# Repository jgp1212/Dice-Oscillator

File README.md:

# Dice-Oscillator
A simple pcb design for a 40106 square wave oscillator drone.

NOTE: This Readme is still a work in progress

Control 6 oscillators using 6 potentiometers. 

Additional pins have been exposed to allow for potential vactrol implementations, or maybe you have a potentiometer that doesnt fit the footprint. 
Use cables to solder to these points.

Can be powered by 5-12V, using 5V will output roughly ~4Vpp, while 12V will output a 10Vpp.
Power supply must be center positive, I have blown up several CD40106BE by accident by using center negative by accident.

BOM:
-  1 x CD40106BE IC
  - 

-  1 x 2.1mm Power jack OR 1 x 16 pin eurorackstyle header. USE ONLY ONE OPTION WHEN POWERING.
  - 

-  7 x 10K Ohm Resistors
-  1 x 8.2K Ohm Resistor
-  6 x 10K Potentiometers
-  6 x 4.7uF Capacitors (can be altered for different audio)
-  6 x 2 pin jumpers. OR 6 toggle switches whch can be wired in place of the jumpers.

-  1 x LED
-  1 x 510Ohm Resistor
-  1 x 3.5mm mono jack (WQP-PJ301M-12_JACK from Thonkiconn)
  -

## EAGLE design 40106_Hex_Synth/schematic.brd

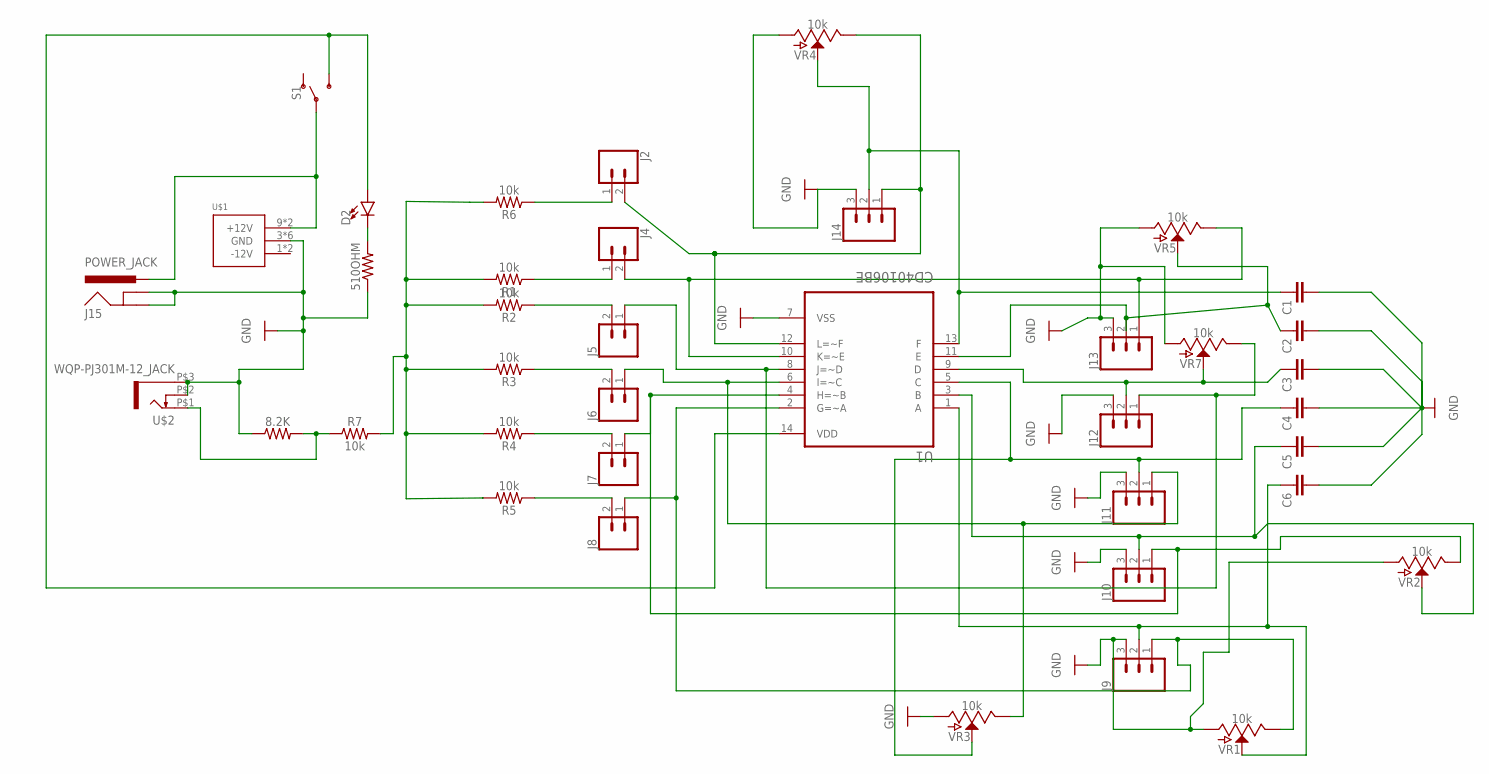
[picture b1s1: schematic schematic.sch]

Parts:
8.2K, 510OHM: AXIAL-0.3
C1, C2, C3, C4, C5, C6: C5/5; C5B5
D2: LED5MM; LED_5MM
J2, J4, J5, J6, J7, J8: CONN_02; 1X02
J9, J10, J11, J12, J13, J14: CONN_03; 1X03
J15: POWER_JACK; POWER_JACK_PTH
R1, R2, R3, R4, R5, R6, R7: 10k; AXIAL-0.3
S1: SWITCH-SPDT-PTH-11.6X4.0MM; SWITCH_SPDT_PTH_11.6X4.0MM
U1: CD40106BE; DIP794W45P254L1969H508Q14
U$1: POWER_SIMPLE16; POWER_16
U$2: WQP-PJ301M-12_JACK
VR1, VR2, VR3, VR4, VR5, VR7: 10k; POT-PTH-ALPS

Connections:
GND: 8.2K.P$1 (1), 510OHM.P$1 (1), C1.2, C2.2, C3.2, C4.2, C5.2, C6.2, J9.3, J10.3, J11.3, J12.3, J13.3, J14.3, J15.GND, J15.GNDBREAK, U1.7 (VSS), U$1.3 (GND), U$1.4 (GND), U$1.5 (GND), U$1.6 (GND), U$1.7 (GND), U$1.8 (GND), U$2.P$2 (3), U$2.P$3 (1), VR1.P$3 (A), VR2.P$3 (A), VR3.P$3 (A), VR4.P$3 (A), VR5.P$3 (A), VR7.P$3 (A)
unnamed: 510OHM.P$2 (2), D2.K (C)
unnamed: C1.1, J14.2, U1.13 (F), VR4.P$2 (S)
unnamed: J2.2, J14.1, U1.12 (L=~F), VR4.P$1 (E)
unnamed: J4.1, R1.P$1 (1)
unnamed: J5.1, J12.1, U1.8 (J=~D), VR7.P$1 (E)
unnamed: C4.1, J11.2, U1.5 (C), VR3.P$2 (S)
unnamed: C5.1, J10.2, U1.3 (B), VR2.P$2 (S)
unnamed: C6.1, J9.2, U1.1 (A), VR1.P$2 (S)
unnamed: C2.1, J13.2, U1.11 (E), VR5.P$2 (S)
unnamed: J5.2, R2.P$1 (1)
unnamed: J8.2, R5.P$1 (1)
unnamed: J7.2, R4.P$1 (1)
unnamed: J6.2, R3.P$1 (1)
unnamed: J2.1, R6.P$1 (1)
unnamed: J4.2, J13.1, U1.10 (K=~E), VR5.P$1 (E)
unnamed: C3.1, J12.2, U1.9 (D), VR7.P$2 (S)
unnamed: J6.1, J11.1, U1.6 (I=~C), VR3.P$1 (E)
unnamed: J7.1, J10.1, U1.4 (H=~B), VR2.P$1 (E)
unnamed: J8.1, J9.1, U1.2 (G=~A), VR1.P$1 (E)
unnamed: 8.2K.P$2 (2), R7.P$1 (1), U$2.P$1 (2)
unnamed: R1.P$2 (2), R2.P$2 (2), R3.P$2 (2), R4.P$2 (2), R5.P$2 (2), R6.P$2 (2), R7.P$2 (2)
unnamed: J15.PWR, S1.2, U$1.9 (+12V), U$1.10 (+12V)
unnamed: D2.A, S1.3 (S), U1.14 (VDD)

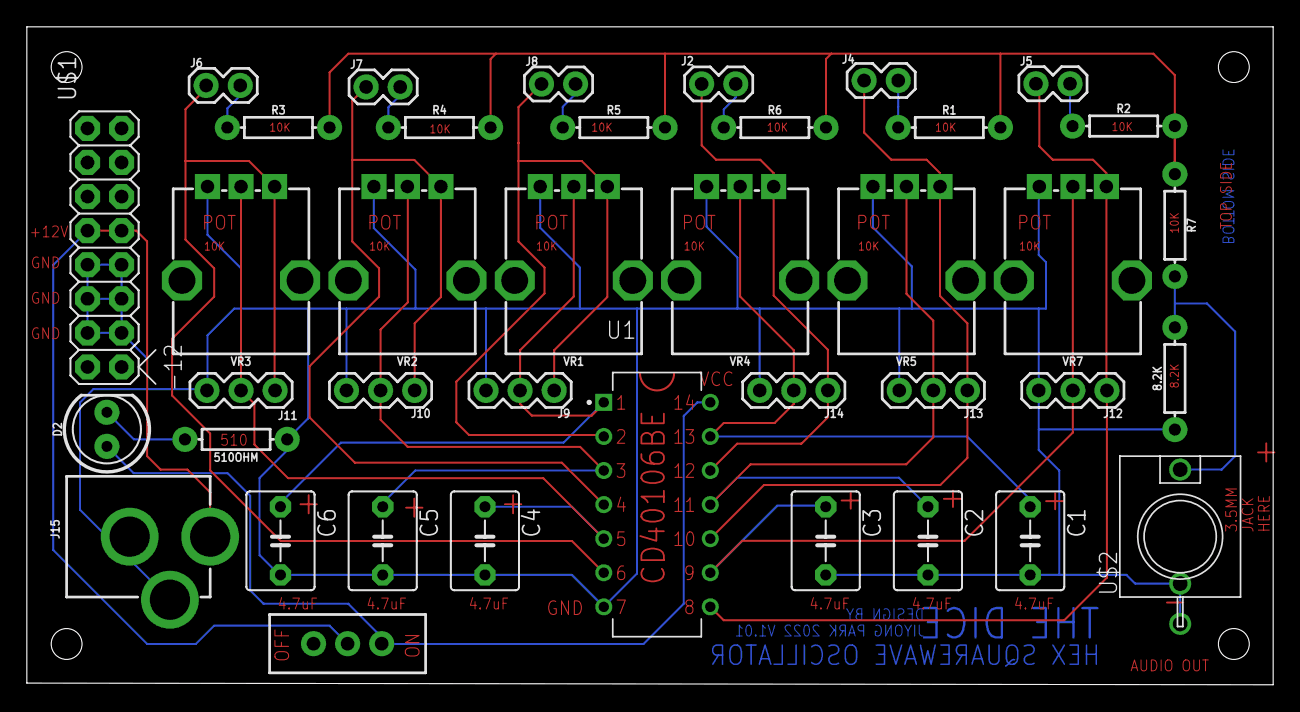
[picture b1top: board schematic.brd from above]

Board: 2 copper layers, 92.9 x 49.0 mm, 39 parts (0 on the bottom side), 24 nets.

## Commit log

2022-09-28 1st pass

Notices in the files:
parts and their libraries:
SparkFun-Connectors: Licensing: Creative Commons ShareAlike 4.0 International - https://creativecommons.org/licenses/by-sa/4.0
